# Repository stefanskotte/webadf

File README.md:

# WebFloppy

An Amiga disk library that puts a disk in a real Amiga's floppy drive over WiFi. (The repository keeps the
project's first name, `webadf`.)

Two halves that work together:

- **A web app** for keeping Amiga disk images. Add them, have them identified
  against TOSEC, OpenRetro and Demozoo, organise them into collections, browse and
  edit the files inside a disk, rewind a disk to any earlier version, and send files to
  and from the Amiga.
- **A drive replacement.** An RP2350 board plugs into the Amiga's floppy connector,
  behaves like a DD or HD floppy drive, and plays whichever disk you pick in the web app.
  When the Amiga saves, the changes go back to the library.

Run the web app two ways: use our hosted copy at <https://webadf.vercel.app> (on Vercel), or
host your own with Docker on any amd64 or arm64 machine, a NAS included. A self-hosted copy has every
feature the hosted one has. Firmware updates, the PaulaNET driver disk and the TOSEC catalogue
arrive by themselves; see [docs/self-hosting.md](docs/self-hosting.md).

Pick a disk in the browser, or tap its NFC tag on the drive, and the Amiga reads it.
Workbench 3.1 boots from the board, games load, and saves made on the Amiga show up
in the web app as new versions of the disk.

*Rev B, designed by Shanshe: 34-pin floppy header, floppy power connector, OLED
display, buzzer, a 4-pin header (J4), and a Pimoroni Pico Plus 2 W.
The KiCad project is in `wifi-floppy/hardware/`; check it with `pnpm hw:verify` before
ordering. Rev B has been the bench board since October 2026.*

## Bugs and ideas

Found a bug, or want something WebFloppy does not do yet? Anyone can open an issue at
<https://github.com/stefanskotte/webadf/issues>, for a bug report or a feature request alike. For a bug, say what
you did, what you saw and, for a board, which firmware it runs (Devices shows it).

## Quickstart

Choose where the web app runs. The board's first install is the same either way; only a
self-hosted copy needs one extra step, pointing the board at your server.

### Path A: the hosted web app (Vercel)

You need the board, a USB cable, a phone and an account on <https://webadf.vercel.app>
(registration is by invitation). The board talks to this server out of the box.

1. Hold the **BOOT** button (the Raspberry Pi docs call it BOOTSEL) and plug the board into
   your computer over USB. A drive called `RP2350` appears.
2. Download `wifi-floppy-install-<version>.uf2` from the
   [latest release](https://github.com/stefanskotte/webadf/releases/latest) and drag it onto
   that drive. The board writes it and restarts by itself; the drive disappears.
3. **Get a pairing code in the web app.** The code comes from the web app, not the board. Open
   **Devices**: with no board yet it lists the five steps (**How pairing works** shows them again at any
   time). Press **Pair a device**, give the board a name and press **Get a code**. The code lasts 30 minutes,
   and the page now walks you through the rest with the code filled in.

4. **Give the board your Wi-Fi and the code.** Power the board; its screen shows *Setup needed* and its own
   Wi-Fi network, `wifi-floppy-XXXX`. Join that network from your phone (password `wififloppy`). The
   setup page opens by itself; if it does not, browse to `http://192.168.4.1/`. Enter your home Wi-Fi name
   and password (a 2.4 GHz network with a password) and the code, and press **Save**.

5. **Wait about a minute.** The board's network disappears, the board joins your Wi-Fi and uses the code
   to register with the web app. Keep the Devices page open: it says **Paired** and shows the board by
   itself. If the board cannot join or register, its setup network comes back with the reason at the top
   of the setup page; join it again and fix that. Firmware updates now arrive over the air from the web app.

### Path B: your own server (self-hosted, Docker)

You need a host with Docker and Compose v2, the board, a USB cable and a phone.

1. Install the stack, as [docs/self-hosting.md](docs/self-hosting.md#2-install) describes: download
   `compose.yaml` and `.env.example` (as `.env`) from the newest `web-X.Y.Z` tag, set `WEBADF_URL`
   (for example `https://192.168.1.10`) and `WEBADF_ADMIN_EMAIL` in `.env`, then run
   `docker compose up -d`. Create the account with the link from `docker compose logs app | grep 'first admin'`.
2. Install the firmware as in steps 1-2 of Path A.
3. **Override the server.** The firmware points at the hosted app by default. Open the board's
   USB serial console (any serial terminal, firmware 1.13.0 or newer) and type:

   ```
   wf server set https://192.168.1.10
   wf server tls noverify
   YES
   wf reboot
   ```

   Use your own `WEBADF_URL`. `tls noverify` is needed because a board cannot trust the
   certificate Caddy makes for an IP address or a LAN name; with a public `WEBADF_DOMAIN` and a
   Let's Encrypt certificate, leave it out. `wf server show` prints the setting and
   `wf server clear` goes back to the hosted app. Changing the server forgets the board's
   Wi-Fi and pairing, and it refuses while a disk is mounted.
4. Pair it as in steps 3-5 of Path A, from **Devices** on your own server. Firmware updates come
   from your server too: it imports every signed release from GitHub daily.

If your phone has joined this board's setup network before, forget that network first. More
detail, and what to do when a join fails, is in
[wifi-floppy/README.md](wifi-floppy/README.md#first-install) and, for a self-hosted copy,
[docs/self-hosting.md](docs/self-hosting.md#4-boards).

## Screenshots

The pictures come from a demo account holding freely redistributable disks: scene demos and
freeware tools. `PORT=3100 pnpm screenshots` takes them again (see
`e2e/screenshots.shots.ts`); every email address on them is masked, and the board is a
stand-in called A500. The one exception is Transfer's window, captured from a real A500 by hand.

*The library. Titles are identified against TOSEC and Demozoo; the 9 Fingers card is
outlined and carries a DF0 pill because its disk is in a drive.*

*The drive menu in the header: from any page, see what each board is playing, switch write
protection, step to the next disk or eject.*

*A title page: facts and screenshots from Demozoo, then each disk with its actions.*

*Files: two panes in the Directory Opus style over STASH:, NET: and LIBRARY: (collections are folders there). The pane
you last clicked is the source; the buttons under the panes act on it. Each edit to a disk is a new version in its History.*

*NET: also lists the Amiga's own volumes when Transfer runs there with Read ticked: open a drawer on the hard disk
and copy files to STASH: or LIBRARY:. With Write ticked too, copy and move onto it, rename and delete.*

*Transfer, on the Amiga itself: files from the web app arrive here, and Send goes the other way. Read and Write decide
what the web app may do with the Amiga's volumes.*

*A board on the Devices page. The drawing's screen shows what the board's OLED shows.*

*The display editor: choose the panel, then which elements the OLED draws and where.*

*Adding disks: drop them anywhere on the Library page, or use Add disks (Browse files, Paste a URL). The tray says
what each one did.*

*Help explains the parts that are not obvious.*

*Settings has three tabs: Account (yours alone), Library (sharing) and Server.*

*Sharing, on the Library tab: let a friend's WebFloppy browse and mount your collections. Each link works once.*

*About this server, on the Server tab.*

*On a phone or a tablet (below 1024 px wide), the pages move to a tab bar at the bottom; More holds the rest.*

*The server admin's Overview, for whoever runs the copy.*

## Features

### Library

- Add `.adf`, `.adz`, `.dms`, `.dmz` and `.hfe` by dropping them anywhere on the Library page (folders and
  `.zip` / `.lha` of them too) or through Add disks: Browse files, or Paste a URL to one (or to a `.zip` or `.lha`
  of them, up to 20 MB). Drop `.lha`, `.lzh` and `.zip` archives onto a disk to pick files out of them.
- HD (1.76 MB) ADFs are recognised and tagged HD, and are disks like any other: browsed
  and edited in the browser, with full history.
- Each unique disk is stored once, however many times it is added.
- Disks are identified against TOSEC, OpenRetro and Demozoo, and grouped into titles
  with cover art, screenshots, publisher, year and type.
- A grid of cards or a condensed table, a page at a time; collections (folders in the table),
  disk sets for multi-disk games, and search from the header.
- Create a blank formatted disk: 880 KB or 1.76 MB, OFS or FFS.
- Download any disk as an ADF.
- Works on a phone: below 1024 px the pages move to a tab bar at the bottom.

### Files

- The Files page: two panes over three places. LIBRARY: holds your titles and their disks; STASH: keeps loose
  files for 30 days (what you drop there, and what your Amiga sends); NET: holds what waits to go to each board's
  Amiga, and the Amiga's own volumes. Copy and move between the panes, or drag.
- Browse the AmigaDOS filesystem in the browser: files, folders, free space.
- Add, rename, move and delete files and folders; drop a folder from your computer
  onto a disk; drag entries between folders.
- Every change is a new version. The history panel shows what changed in each
  version, lets you browse any old version, and restores one as a new version.
- HFE images (including long-track formats such as Turrican's) play read-only and can
  be extracted to an ADF when every sector decodes.

### The drive

- Set up from a phone: the board opens a WiFi setup page, you enter your network and
  a pairing code from the web app, and it joins your library.
- Mount and eject from the web app, from the drive menu in the header, or by
  tapping an NFC tag. Next disk steps a multi-disk game on, and the board loads that disk
  ahead of time.
- Reads and writes on a real Amiga. Saves reach the library as new disk versions,
  including saves made while the board was offline.
- Works as DF0, beside a real DF1. Or the board is DF1 as well: holding the next disk of the
  set, or any disk you mount there.
- Plays HD disks: the board tells the Amiga it is an HD drive while an HD disk is in.
  Needs Kickstart 3.0 or later. Playing needs firmware 1.4.1 or later (the web app
  refuses to mount an HD disk on older firmware and says so); saving to an HD disk
  needs 1.5.0 (1.4.x keeps HD write-protected on the board whatever the web app
  says).
- Write protection can be switched from the web app while the disk is in the drive.
- OLED status display (128x32 or 128x64, SSD1306 or SH1106): WiFi strength, what it is
  doing, the disk's name and the current track. A display editor in the web app picks what
  it shows and where. An activity LED blinks on reads.
- Updates its own firmware from the web app. Releases are signed, a failed update
  falls back to the previous firmware, and the board never updates while a disk is
  in the drive.

### Amiga networking

- The board can put the Amiga on your network as DF1, with Rob Smith's PaulaNET driver
  (used with his permission) and a TCP/IP stack such as AmiTCP_NG or Roadshow. The driver disk
  comes from the board itself.
- Send files from your computer, or from a disk in your library, to a folder on the Amiga: on the Files page,
  drop them on Send files to the Amiga, or copy them into a board under NET:. Files the Amiga sends back land in STASH:.
- Transfer, the Amiga program on the driver disk, saves what arrives and sends files up. It runs from Workbench,
  from a Shell, or hidden from WBStartup as a commodity (Ctrl-Alt-W shows it).
- With Transfer's Read ticked, the Files page browses the Amiga's own volumes; with Write ticked too, it copies and
  moves onto them, makes drawers, renames and deletes. Both are off until the Amiga's owner ticks them.
- Setting it up, Transfer, the limits and what to do when something fails:
  [docs/amiga-networking.md](docs/amiga-networking.md).

### NFC tags

- Tap a tag on the drive to mount its disk. Tapping another tag swaps disks; tapping
  the one already in the drive does nothing. A Next-disk card steps to the next disk.
- Write any disk to a tag from the ⋯ menu on its library card, or the NFC button on a
  disk, then tap a tag on the drive; the result appears in the browser.
- A tag only ever mounts disks from your own library.
- Reader: HW-147C (Si512), on the board's I2C bus next to the OLED. PN532 modules work
  from firmware 1.18.0 and are still being tested.

## How it works

An Amiga floppy drive does not deliver blocks. It hands Paula a raw magnetic flux
stream and the Amiga decodes MFM in software, so a drive emulator has to produce flux
at the right rate, continuously, while the disk spins.

```
  browser  ──mount──▶  web app  ──encodes ADF → MFM──▶  device  ──flux──▶  Amiga
     ▲                    │                                │
     └──── new version ◀──┴── Postgres + blobs     RP2350 + 8 MB PSRAM ◀── NFC tag
```

The server encodes a 901,120-byte ADF into 2,027,536 bytes of Amiga MFM and the board
streams it: PIO emits 2 µs bitcells, DMA restarts each revolution and raises INDEX,
giving 300 rpm. The whole disk lives in PSRAM, so a seek is answered immediately
instead of over the network. The board streams flux rather than ADFs, which lets
flux formats such as HFE use the same path.

An HD disk is the exception. The server sends the board the ADF itself (a small
WFAD header, then 1,802,240 bytes), and the board encodes each track to MFM as the
head reaches it, in about 4 ms, well inside the head's settle time. A PIO program
answers the Amiga's drive-ID read on RDY with the HD ID while an HD disk is mounted.
When the Amiga saves to an HD disk, the board checks all 22 sectors of the written
track, keeps them as ADF bytes, and uploads those bytes as they are.

When the Amiga writes, the board decodes the written tracks, uploads them, and the
server records them as a new version of the disk. Versions are stored as sector
deltas.

## Status

| | |
|---|---|
| Web app: library, collections, identification, search | live |
| Add `.adf` `.adz` `.dms` `.hfe` to the library; `.lha`/`.lzh`/`.zip` onto a disk | live |
| File editing inside a disk, blank disks, drag and drop | live |
| Disk history: browse and restore any version | live, restore verified on hardware |
| Device: setup portal, WiFi, TLS, pairing | verified on hardware |
| Mount and eject from the browser and the header's drive menu | verified on hardware |
| Reading on a real Amiga (Workbench 3.1, games) | verified on hardware |
| Writing on a real Amiga, saves reach the library | verified on hardware |
| Second drive (DF1) alongside the board | verified on hardware |
| HFE, including long-track (Turrican) | verified on hardware; weak-bit titles not yet tested |
| HD disks, read-only (Kickstart 3.0+) | verified on hardware (firmware 1.4.1, Kickstart 3.1) |
| HD disks: Amiga saves, history, browser editing, blank HD disks | shipped in firmware 1.5.1; bench steps 4-7 owed (HANDOFF 3ao) |
| Firmware updates from the web app | verified on hardware (current release: 1.21.1) |
| Self-hosting with Docker (compose stack, GHCR image, amd64 + arm64) | live (web-1.1.0); verified with a board and an A500 on an openmediavault NAS |
| NFC: tap to mount, write tags from the web | verified on hardware |
| Amiga networking (PaulaNET as DF1), files to and from the Amiga | verified on hardware (A500) |
| Rev B board | built and running (Shanshe's design, `wifi-floppy/hardware/`) |

## Repository

| Path | What |
|---|---|
| `src/` | the Next.js app |
| `src/lib/adfmfm/` | ADF ⇄ Amiga MFM encoder, verified against Greaseweazle |
| `src/lib/adffs/` | AmigaDOS filesystem reader/writer (OFS/FFS) |
| `src/lib/archive/` | `.lha`/`.lzh`, `.zip` and `.dms` decoders, all browser-side |
| `src/lib/hfe/` | HFE parsing, conversion for the board, ADF extraction |
| `src/lib/disk-history/` | sector deltas and the version chain behind history and restore |
| `src/lib/nfc/` | NFC tap and tag-writing rules and storage |
| `wifi-floppy/firmware/` | the RP2350 firmware (pico-sdk ≥ 2.3.0) |
| `wifi-floppy/hardware/` | the board (KiCad) |
| `docs/superpowers/specs/` | design specs, one per feature |
| `HANDOFF.md` | the engineering log: decisions, measurements, bench results |

## Running it

```bash
pnpm install
pnpm db:dev start         # a local Postgres 18 in Docker; prints its DATABASE_URL
pnpm db:migrate           # apply drizzle/ to DATABASE_URL (there is no db:push)
pnpm dev                  # needs .env.local: DATABASE_URL, BETTER_AUTH_SECRET,
                          # BETTER_AUTH_URL (BLOB_READ_WRITE_TOKEN is optional)
pnpm test                 # vitest, pure logic
pnpm e2e                  # playwright, against the database in .env.local
bash scripts/e2e-local.sh # playwright with no Vercel or Neon: a fresh Postgres in
                          # its own container (webadf-pg-e2e, :55433 -- never the
                          # db:dev one) and local storage; arguments go to playwright
```

Stored files (disk images, covers, firmware) go to local disk under `./data/blobs`
(`STORAGE_DIR` moves it) unless `BLOB_READ_WRITE_TOKEN` is set, in which case they go to
Vercel Blob. On Vercel the token is required: the app refuses to fall back to local disk there.

To run your own copy, use the Docker stack in [docs/self-hosting.md](docs/self-hosting.md)
(Quickstart, [Path B](#path-b-your-own-server-self-hosted-docker)); the commands above are for development.

A self-hosted copy needs no extra setting: Settings → About this server (`/about` leads there) reads
**Self-hosted** unless `SELFHOSTED=false`, which only our own deployment sets. A Docker build
without `.git` can pass `GIT_SHA` so About this server shows the commit.

Firmware:

```bash
export PICO_SDK_PATH=/path/to/pico-sdk        # tag 2.3.0 or later
pnpm firmware:build
pnpm firmware:test                            # host tests, no board needed
pnpm firmware:publish --dry-run               # sign and register a release
```

Write a disk to an NFC tag from the command line:

```bash
pnpm nfc:write "Turrican II disk 1"           # then tap a tag on the drive
```

The setup access point uses the password **`wififloppy`** by default. Set
`PORTAL_AP_PASSWORD` at build time to change it. The pairing code from the web app is
what authorises a board to join a library.

Putting the firmware on a new board is the [Quickstart](#quickstart) above: one
`wifi-floppy-install-<version>.uf2` from the GitHub release, dragged onto the drive that
appears while BOOT is held at power-up. With picotool, `pnpm firmware:install-partitioned` still works.

Every push that touches the firmware is built by
[`.github/workflows/firmware.yml`](.github/workflows/firmware.yml), which runs the host
tests and publishes a `.uf2` with a `manifest.json` (version, commit, size, SHA-256).

## Verification

Each layer that talks to hardware or to an undocumented format is checked against an
independent implementation:

| | checked against |
|---|---|
| `pnpm adfmfm:diff` | Greaseweazle's `amigados` codec |
| `pnpm adffs:verify` | `xdftool` |
| `pnpm lha:verify` | the real `lha` binary |
| `pnpm dms:verify` | xDMS, the implementation ours was ported from |

## Licence

- **Software** (the web app, scripts and the wifi-floppy firmware source): [MIT](LICENSE).
- **Hardware** (`wifi-floppy/hardware/`, the board design): [CERN-OHL-P-2.0](wifi-floppy/hardware/LICENSE), the
  permissive open-hardware licence, so anyone can build, modify and sell their own boards. The rev B PCB layout is
  Shanshe's work, licensed this way with Shanshe's agreement; see
  [wifi-floppy/hardware/NOTICE.md](wifi-floppy/hardware/NOTICE.md).
- **Third-party code, the libraries in the firmware image, and acknowledgements**: see
  [THIRD-PARTY-NOTICES.md](THIRD-PARTY-NOTICES.md). The Wi-Fi driver bundled with the Pico SDK is licensed for use
  on Raspberry Pi chips (which this board is).

This project builds on Nano-Tek, OpenFlops, Keir Fraser's FlashFloppy and Greaseweazle, and the other work credited
in the notices file.

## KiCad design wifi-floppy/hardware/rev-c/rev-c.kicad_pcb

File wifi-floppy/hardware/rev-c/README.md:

# Rev C: on-board RP2350, schematic and routed board

Rev B with the PIM726 module replaced by its parts on our PCB: RP2350B, 16 MB flash, 16 MB PSRAM, RM2 radio, crystal, core regulator, USB-C, BOOTSEL, SWD. Every GPIO stays where the PIM726 has it, so the firmware's pin map and the pico-sdk board definition are unchanged. Same outline as rev B. Rev B's files are untouched.

**The schematic and the routed board agree, and nothing else about the board differs from using a PIM726 on rev B. It is still not a board to order:** see "Owed before a fab order".

## Result (2026-11-05)

| Check | Result |
|---|---|
| Layers | 4: signals on F.Cu and B.Cu, GND on In1, +3.3 V on In2 |
| KiCad DRC, with schematic parity | 0 unconnected, 0 errors, 0 parity differences. 24 silkscreen warnings, 21 of them M1's outline over its own pads, and one 0.03 mm neck somewhere in the top ground pour, not located |
| ERC | 0 errors, 0 warnings |
| `verify_sch.py` | all 75 multi-pin nets match, whatever they are called |
| `verify_pins.py rev-c.kicad_pcb` | 209 of 209 against the RP2350 datasheet, firmware `board.c`, the pico-sdk header, the RM2 datasheet, and rev B's connected pads |
| `verify_reg.py` | the regulator matches Raspberry Pi's pattern: 62 differences before, 0 now |
| `pnpm hw:verify rev-c` | passes: ERC, DRC, firmware pins, J1 lines, 1k pull-ups, the regulator |
| Gerbers | analysed with kicad-happy. Not yet through JLC's own check |
| Tracks | 0.15 mm, necked as low as 0.09 mm at the QFN, vias 0.45/0.2 mm, spacing 0.127 mm: within JLC's published 4-layer limits, not confirmed by JLC |

## Parts

From Pimoroni's Pico Plus 2 W schematic unless noted.

| Ref | Part | Note |
|---|---|---|
| U1 | RP2350B, QFN-80 | |
| U3 | W25Q128JVSIQ, SOIC-8 208 mil | Pimoroni's schematic names W25Q128JVPIQ: same family and capacity, check the package suffix when buying |
| U4 | IS66WVS16M8FBLL-104NLI, SOIC-8 150 mil | **16 MB, not Pimoroni's 8 MB.** APS6404L-3SQR is pin-compatible and fits the same pads |
| M1 | Raspberry Pi RM2 | Own antenna. Hand-made footprint from RM2 datasheet figure 6 |
| U5 | NCP1117ST33T3G, SOT-223 | **Not Pimoroni's AP7366** (the 2026-10-20 rev C note's part, easier to solder and cool) |
| L1 | Abracon AOTA-B201610S3R3-101-T | Raspberry Pi's polarity-marked inductor, LCSC C42411119. **Not Pimoroni's MLZ2012M3R3HT000**: see "Core regulator" |
| Y1 | Abracon ABM8-272-T3, 15 pF load caps | Raspberry Pi's crystal, LCSC C20625731; JLC's RP2350B page names the same one |

Left out as nothing here uses them: the VSYS sense divider and its MOSFET, the 1k links from GP26-28 to GP40-42, the user switch, the Qw/ST connector (its GP4/GP5 are MTR and DIR here; operator confirmed 2026-11-05), the 40-pin header.

The reset button is out (operator, 2026-11-05: BOOTSEL is needed, PIM726's RESET is not). Test pad TP1 on RUN replaces it; RUN keeps its internal pull-up (RP2350 pin table), as on Pimoroni's sheet.

**Scope (operator, 2026-11-05): everything stays as it is with a PIM726.** So the J5 DRIVE passthrough, Amiga RESET line and keyed I2C connectors from the earlier rev C plan are not on this board. Firmware does not use what is left out: GP26-28, GP43 and GP45 appear in comments only.

## Schematic

`rev-c.kicad_sch` is rev B's sheet with the module out. `mcu.kicad_sch` (RP2350B, supplies, crystal, RM2) and `support.kicad_sch` (USB-C, 3.3 V, flash, PSRAM, BOOTSEL, debug) hold the module's parts, after Pimoroni's sheets. `rev-c-schematic.pdf` is the print. All new symbols are in `rev-c-lib.kicad_sym`; apart from RM2 (drawn from RM2 table 2) and the PSRAM (KiCad's APS6404L with ISSI's value) they are KiCad's own.

The sheets are the source: edit them in KiCad. `build_board.py` reads their netlist for names, values, footprints and links, which is why parity is clean. Swapping MTR and DIR, or removing a PWR_FLAG and a no-connect, in a copy made `verify_sch.py` fail, as it should.

Differences from Pimoroni: the core regulator and crystal (below), NCP1117 with 10 uF either side (AP7366, 2.2 uF; the 2026-10-20 note's part), 16 MB PSRAM, 10 uF added at RM2's VDDBAT, BOOTSEL as 1k and switch without their diode and user-switch network. Pull-ups (flash CS 3k3, PSRAM CS 100k) and the USB series resistors (27.4 ohm) are Pimoroni's.

## Core regulator

Operator's decision, 2026-11-05: Raspberry Pi's pattern, an exception to "same as a PIM726". `reg_pattern.py` holds it, taken from Raspberry Pi's RP2350 minimal design R4 (MIT, see `../NOTICE.md`) and datasheet section 6.3.8; `verify_reg.py` checks the board and sheets against it. The VREG pins have the same order and pitch on our QFN-80 as on the QFN-60 it was drawn for.

| | Pimoroni's sheet, and rev C before | Now | Datasheet |
|---|---|---|---|
| L1 | MLZ2012M3R3HT000, about 350 mA, 260 mOhm max, unmarked | AOTA-B201610S3R3-101-T, 2.4 A, 140 mOhm max, marked | at least 1.5 A, at most 250 mOhm, polarity-marked |
| COUT, C23 | 10 uF | 4.7 uF | 4.7 uF +/-20% |
| CIN, C21 | 10 uF | 4.7 uF | at least 4.7 uF |
| RFILT, CFILT (R20, C22) | 27.4 ohm, 2.2 uF | 33 ohm, 4.7 uF | Raspberry Pi's design |
| Second COUT, C15 at DVDD pin 32 | 100 nF | 4.7 uF | recommended |

LX is 4.0 mm on the top layer with no vias. In1 is cut away under L1 and LX (figure 24). The top pour stays out, so the regulator's high-current ground meets the rest at two vias, and CFILT has its own via. VREG_FB comes from COUT, and COUT reaches the DVDD ring by a 0.6 mm track on the back, as Raspberry Pi route it. Moving one of these parts means moving them all.

**L1 has a right way round.** Pad 1, the dot, goes to DVDD: the symbol was flipped so its pin 1 is DVDD. RPROM's README warns that JLC's placement file needed L1's orientation fixing by hand: check it on the assembly preview.

The pattern is copied, not proven here: Raspberry Pi test it on their board, and no rev C board has been built. CIN and COUT need low ESR (50 and 250 mOhm); Raspberry Pi use GRM155R60J475ME47D for all three 4.7 uF parts.

## RM2 antenna

The module sits in the bottom right corner with its antenna on the board edge. Of Raspberry Pi's 35.5 x 18.5 mm keep-out, only 26 x 5 mm is on the board; the rest is air. It is a rule area on all layers, about where rev B's was. In a case, what is beyond the edge also counts.

## 16 MB PSRAM: what is and is not known

The operator confirms the RP2350B supports 16 MB of PSRAM (2026-11-05). What follows is what was checked here.

From the ISSI datasheet and `hardware_psram/psram.c`: same pinout and commands as the APS6404 (35h, EBh with 6 wait cycles, 38h), 2.7-3.6 V, 1024-byte pages. The pico-sdk's size detection names ISSI's 16 MiB ID, and it breaks bursts at 1024 bytes, so a burst cannot cross the part's two stacked dies (its datasheet forbids that). **None of it has run on hardware.** Firmware needs `PICO_PSRAM_SIZE_BYTES` and `SLOT_COUNT` raised to use more than 8 MB.

## Owed before a fab order

1. **A person reading the schematic.** Nobody has yet.
2. **A person checking the core regulator against datasheet figures 23 and 24**, and the crystal: Y1's placement and tracks are still autorouted, its part and caps are now Raspberry Pi's.
3. **A person reading the autorouted copper:** QSPI lengths, the USB pair (12 Mbit/s, so no impedance control needed, but keep it short), the floppy lines. It has too many vias.
4. **Footprints against samples:** RM2, USB-C, buttons.
5. **Board-edge clearances:** SW1 moved in 0.3 mm, now about 0.55 mm. M1 at the edge is intended.
6. **Sourcing:** not checked. The JLC search was down; JLCONE not used.
7. **Heat:** 5 V to 3.3 V at Wi-Fi peaks is about 0.7 W in U5. Measure it.

## Rebuild

In order, with KiCad's Python and Freerouting 2.5.0: `variants.sh` runs `build_board.py` (places), `regulator.py` (the regulator's copper), `stitch.py` (joins power pins to the planes), Freerouting on the outer layers, and `route.py` (adds the planes and pours), into `v1/`. Then by hand: `clean.py v1/rev-c.kicad_pcb v1/drc1.json` removes the router's stray vias and widens any neck below 0.09 mm, `finish.py` adds fiducials and sets the silkscreen, `verify_pins.py` checks. The fiducials landed at free spots, not in the corners: place them properly in KiCad. Part references on the new parts are hidden until someone places them.

`package.sh` builds `rev-c-kicad-project.zip`: the project with `wifi-floppy-lib` copied in and the library tables pointed at the copies, so it opens anywhere with KiCad 10. Rebuild it after any change.

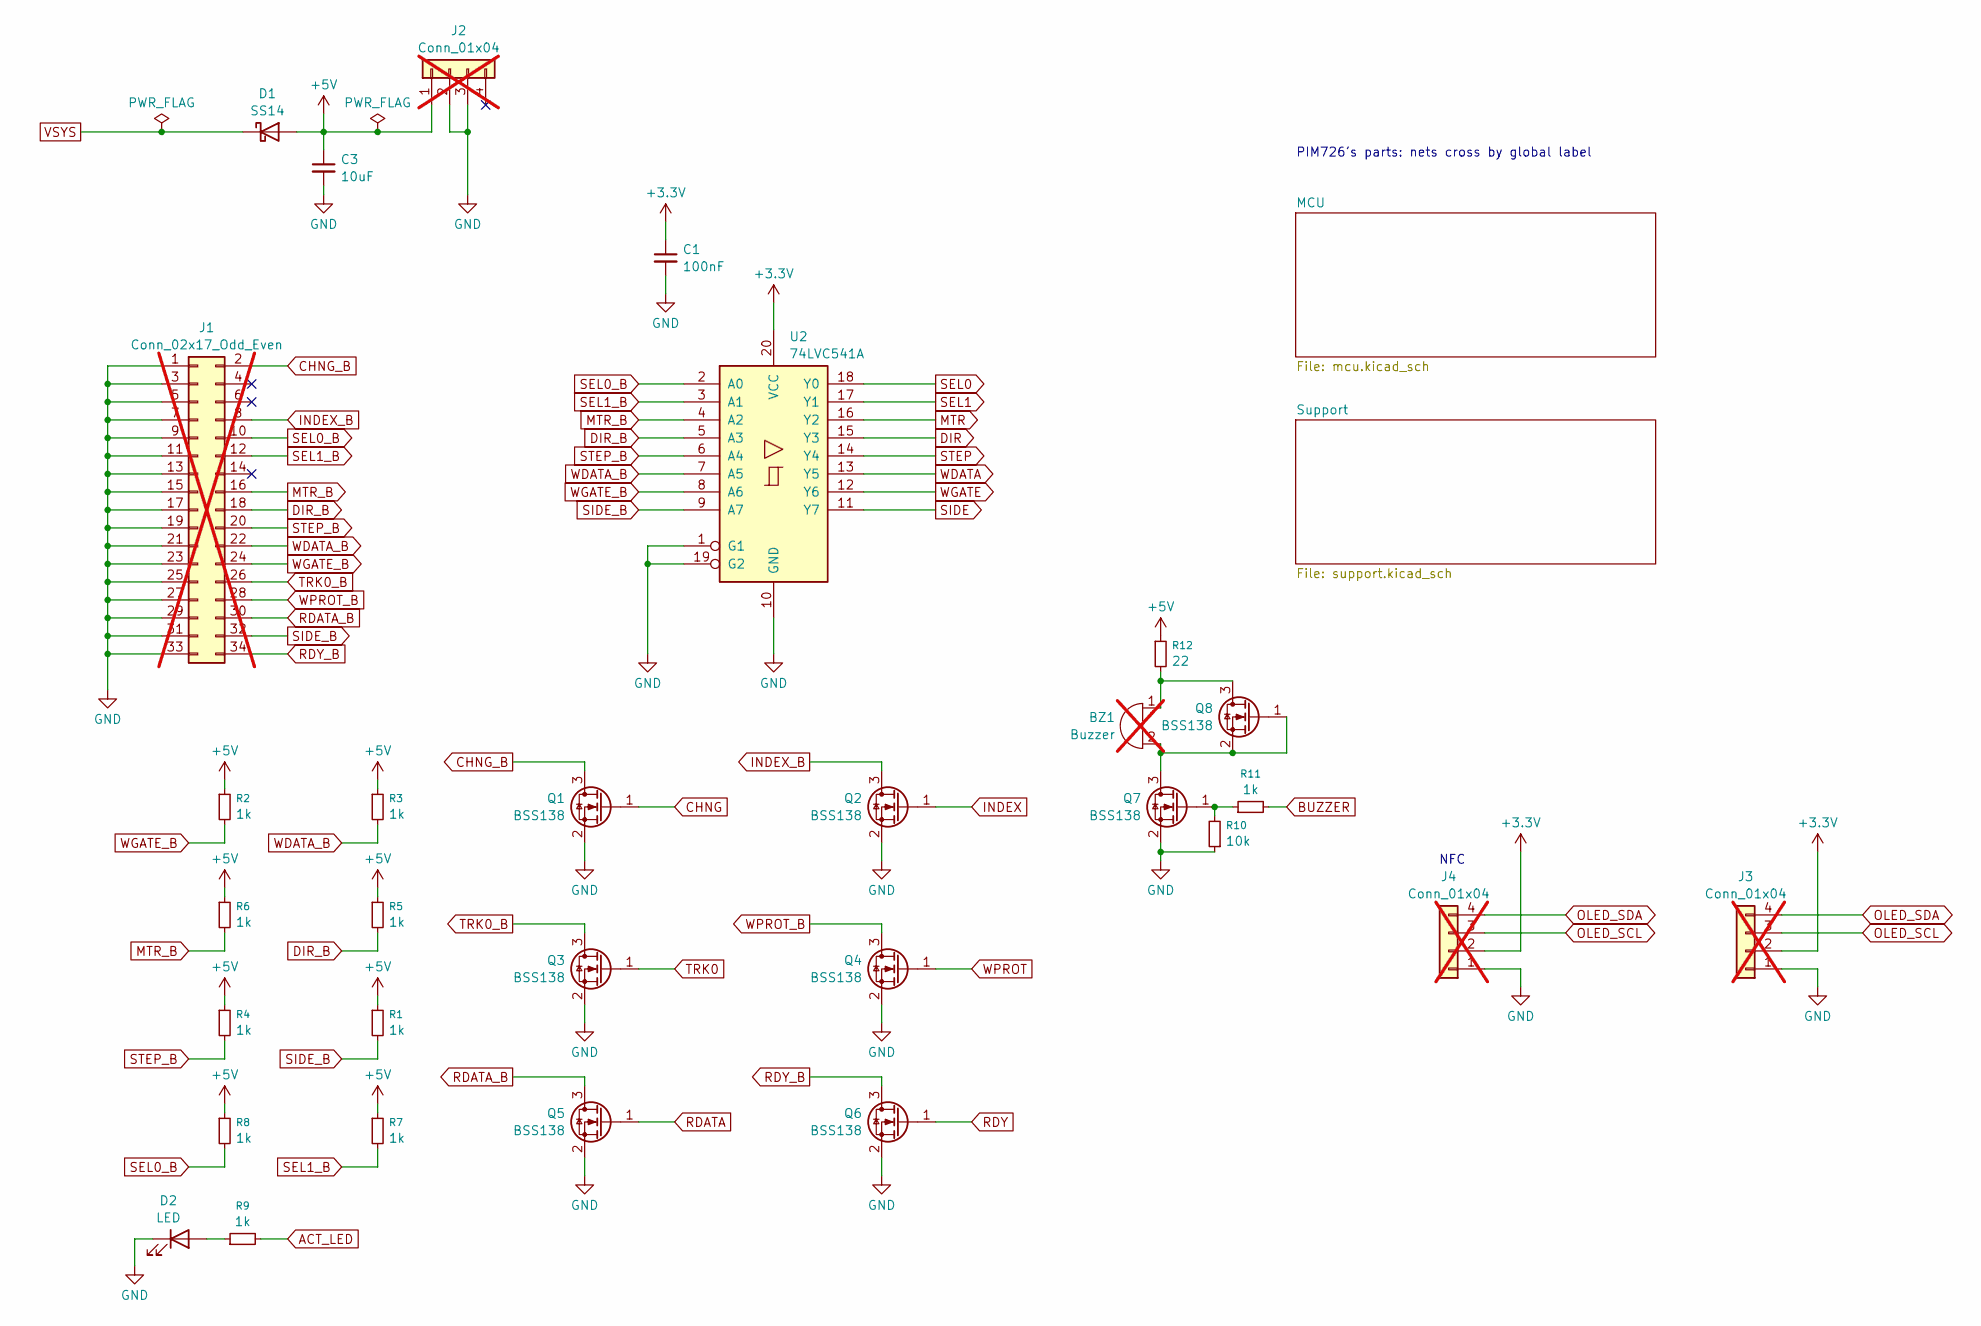
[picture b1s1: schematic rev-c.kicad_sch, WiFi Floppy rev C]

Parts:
BZ1: Buzzer; Buzzer_TDK_PS1240P02BT_D12.2mm_H6.5mm; LCSC C2687681; not fitted
C1: 100nF; C_1206_3216Metric_Pad1.33x1.80mm_HandSolder
C3: 10uF; C_1206_3216Metric_Pad1.33x1.80mm_HandSolder
D1: SS14; D_SMA_Handsoldering
D2: LED; LED_1206_3216Metric_Pad1.42x1.75mm_HandSolder; LCSC C49018
J1: Conn_02x17_Odd_Even; IDC-Header_2x17_P2.54mm_Vertical; LCSC DNP; not fitted
J2: Conn_01x04; PinHeader_1x04_P2.54mm_Horizontal; LCSC DNP; not fitted
J3, J4: Conn_01x04; PinHeader_1x04_P2.54mm_Vertical; LCSC DNP; not fitted
Q1, Q2, Q3, Q4, Q5, Q6, Q7, Q8: BSS138; SOT-23
R1, R2, R3, R4, R5, R6, R7, R8, R9, R11: 1k; R_1206_3216Metric_Pad1.30x1.75mm_HandSolder; LCSC C1469
R10: 10k; R_1206_3216Metric_Pad1.30x1.75mm_HandSolder; LCSC C1489
R12: 22; R_1206_3216Metric_Pad1.30x1.75mm_HandSolder; LCSC C2925020
U2: 74LVC541A; SOIC-20W_7.5x15.4mm_P1.27mm; LCSC DNP

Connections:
+3.3V: C1.1, J3.2, J4.2, U2.20 (VCC); also elsewhere on the board
+5V: C3.1, D1.2 (A), J2.1, R1.1, R2.1, R3.1, R4.1, R5.1, R6.1, R7.1, R8.1, R12.1
ACT_LED: R9.2; also elsewhere on the board
BUZZER: R11.2; also elsewhere on the board
CHNG: Q1.1 (G); also elsewhere on the board
CHNG_B: J1.2, Q1.3 (D)
DIR: U2.15 (Y3); also elsewhere on the board
DIR_B: J1.18, R5.2, U2.5 (A3)
GND: C1.2, C3.2, D2.1 (K), J1.1, J1.3, J1.5, J1.7, J1.9, J1.11, J1.13, J1.15, J1.17, J1.19, J1.21, J1.23, J1.25, J1.27, J1.29, J1.31, J1.33, J2.2, J2.3, J3.1, J4.1, Q1.2 (S), Q2.2 (S), Q3.2 (S), Q4.2 (S), Q5.2 (S), Q6.2 (S), Q7.2 (S), R10.1, U2.1 (G1), U2.10 (GND), U2.19 (G2); also elsewhere on the board
INDEX: Q2.1 (G); also elsewhere on the board
INDEX_B: J1.8, Q2.3 (D)
MTR: U2.16 (Y2); also elsewhere on the board
MTR_B: J1.16, R6.2, U2.4 (A2)
unnamed: BZ1.1 (+), Q8.3 (D), R12.2
unnamed: BZ1.2 (-), Q7.3 (D), Q8.1 (G), Q8.2 (S)
unnamed: D2.2 (A), R9.1
unnamed: Q7.1 (G), R10.2, R11.1
OLED_SCL: J3.3, J4.3; also elsewhere on the board
OLED_SDA: J3.4, J4.4; also elsewhere on the board
RDATA: Q5.1 (G); also elsewhere on the board
RDATA_B: J1.30, Q5.3 (D)
RDY: Q6.1 (G); also elsewhere on the board
RDY_B: J1.34, Q6.3 (D)
SEL0: U2.18 (Y0); also elsewhere on the board
SEL0_B: J1.10, R8.2, U2.2 (A0)
SEL1: U2.17 (Y1); also elsewhere on the board
SEL1_B: J1.12, R7.2, U2.3 (A1)
SIDE: U2.11 (Y7); also elsewhere on the board
SIDE_B: J1.32, R1.2, U2.9 (A7)
STEP: U2.14 (Y4); also elsewhere on the board
STEP_B: J1.20, R4.2, U2.6 (A4)
TRK0: Q3.1 (G); also elsewhere on the board
TRK0_B: J1.26, Q3.3 (D)
VSYS: D1.1 (K); also elsewhere on the board
WDATA: U2.13 (Y5); also elsewhere on the board
WDATA_B: J1.22, R3.2, U2.7 (A5)
WGATE: U2.12 (Y6); also elsewhere on the board
WGATE_B: J1.24, R2.2, U2.8 (A6)
WPROT: Q4.1 (G); also elsewhere on the board
WPROT_B: J1.28, Q4.3 (D)

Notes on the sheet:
PIM726's parts: nets cross by global label
NFC

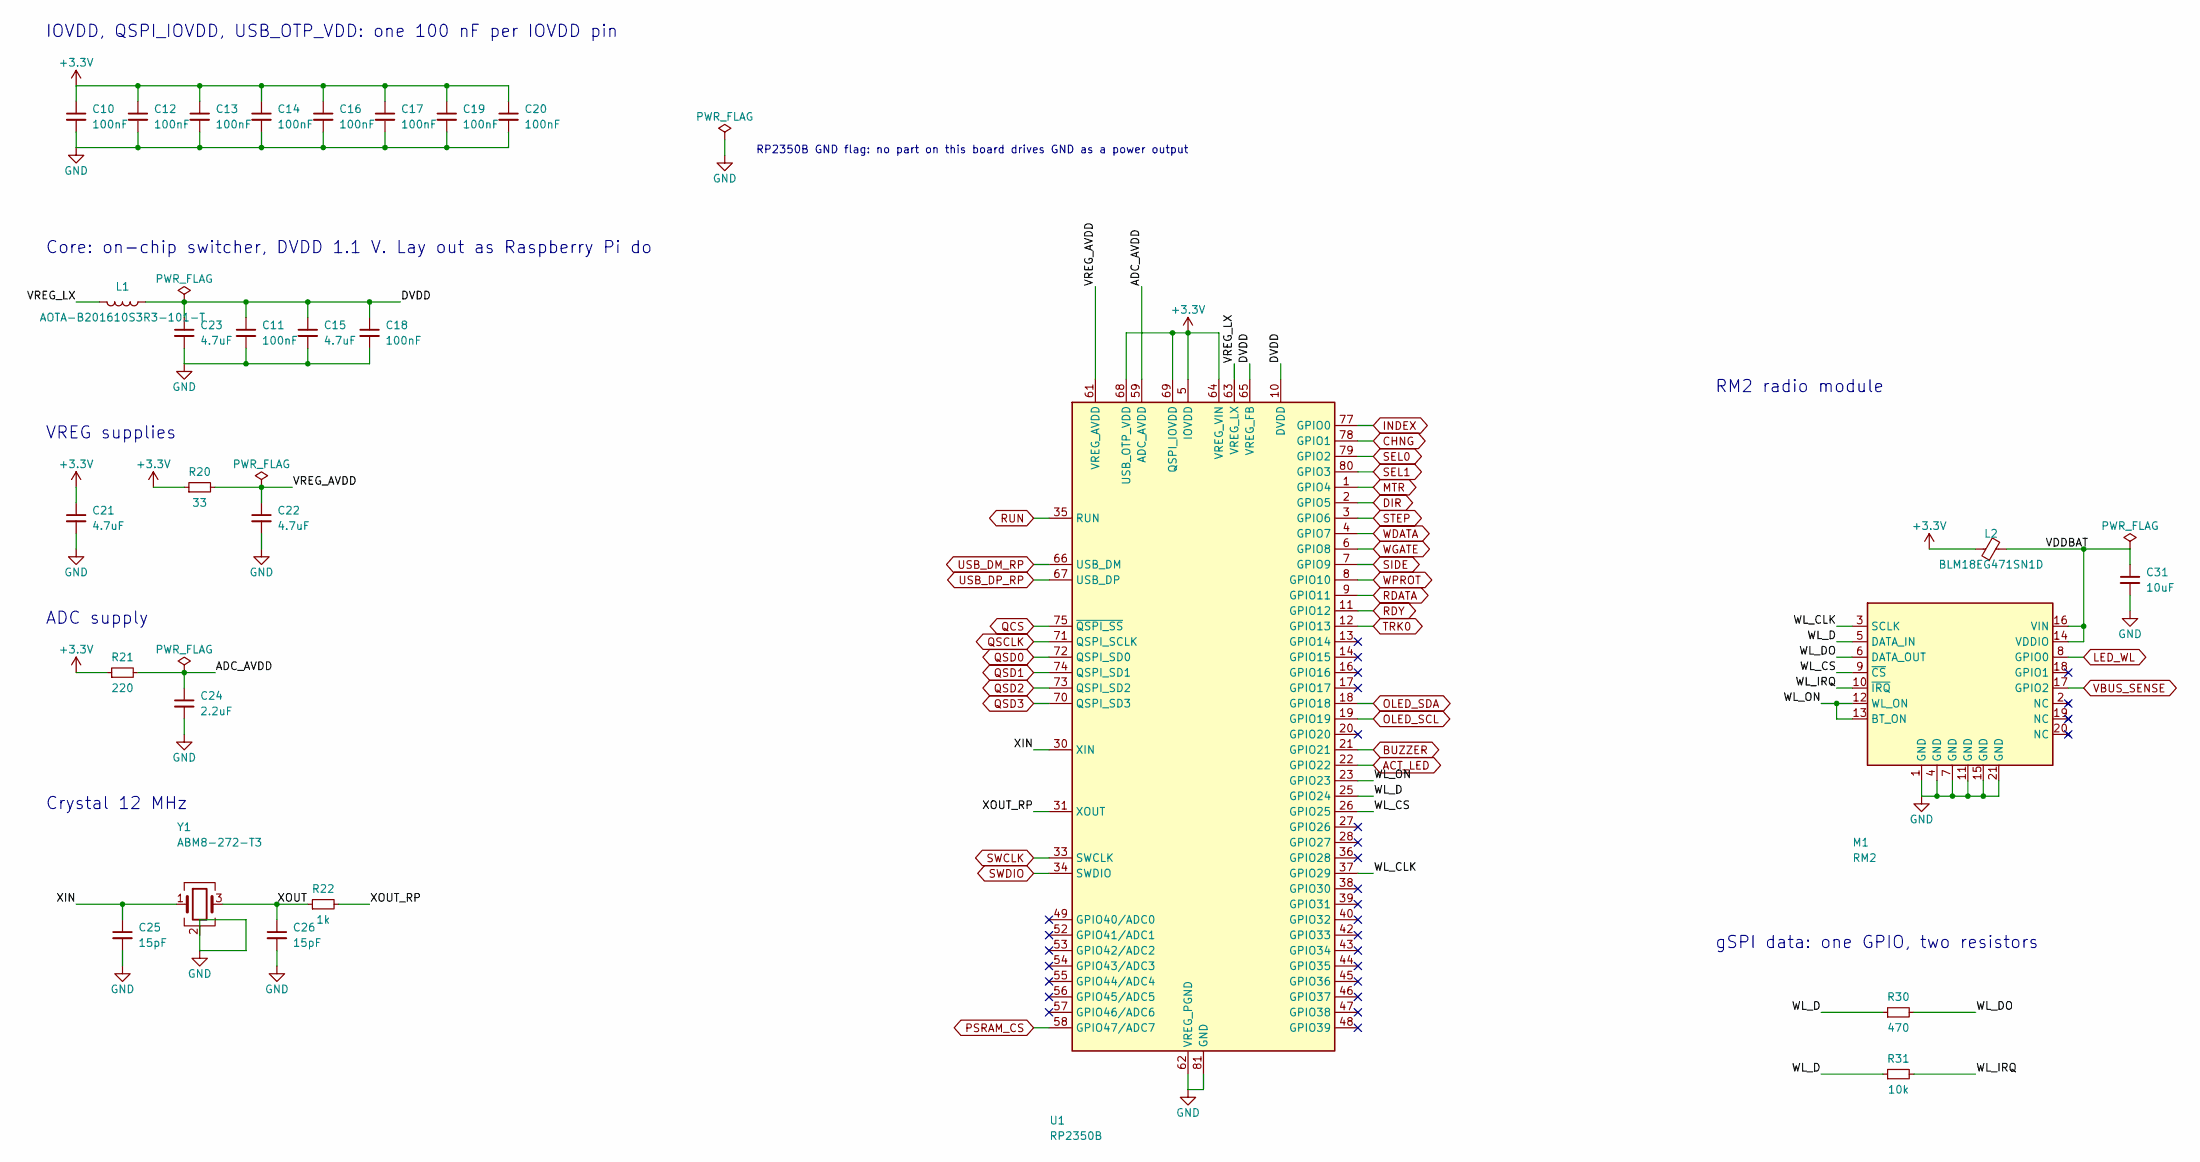
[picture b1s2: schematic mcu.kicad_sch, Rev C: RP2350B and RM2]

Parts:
C10, C11, C12, C13, C14, C16, C17, C18, C19, C20: 100nF; C_0402_1005Metric
C15, C22: 4.7uF; C_0402_1005Metric
C21, C23: 4.7uF; C_0402_1005Metric_RP_wide
C24: 2.2uF; C_0603_1608Metric
C25, C26: 15pF; C_0402_1005Metric
C31: 10uF; C_0603_1608Metric
L1: AOTA-B201610S3R3-101-T; L_Abracon_AOTA-B201610S3R3-101-T; MPN AOTA-B201610S3R3-101-T
L2: BLM18EG471SN1D; L_0603_1608Metric; MPN BLM18EG471SN1D
M1: RM2; Raspberry_Pi_RM2; MPN Raspberry Pi RM2
R20: 33; R_0402_1005Metric
R21: 220; R_0402_1005Metric
R22: 1k; R_0402_1005Metric
R30: 470; R_0402_1005Metric
R31: 10k; R_0402_1005Metric
U1: RP2350B; QFN-80-1EP_10x10mm_P0.4mm_EP3.4x3.4mm_ThermalVias; MPN RP2350B
Y1: ABM8-272-T3; Crystal_SMD_3225-4Pin_3.2x2.5mm

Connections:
+3.3V: C10.1, C12.1, C13.1, C14.1, C16.1, C17.1, C19.1, C20.1, C21.1, L2.1, R20.1, R21.1, U1.5 (IOVDD), U1.15 (IOVDD), U1.24 (IOVDD), U1.29 (IOVDD), U1.41 (IOVDD), U1.50 (IOVDD), U1.60 (IOVDD), U1.64 (VREG_VIN), U1.68 (USB_OTP_VDD), U1.69 (QSPI_IOVDD), U1.76 (IOVDD); also elsewhere on the board
/MCU/ADC_AVDD: C24.1, R21.2, U1.59 (ADC_AVDD)
/MCU/DVDD: C11.1, C15.1, C18.1, C23.1, L1.1, U1.10 (DVDD), U1.32 (DVDD), U1.51 (DVDD), U1.65 (VREG_FB)
/MCU/VDDBAT: C31.1, L2.2, M1.14 (VDDIO), M1.16 (VIN)
/MCU/VREG_AVDD: C22.1, R20.2, U1.61 (VREG_AVDD)
/MCU/VREG_LX: L1.2, U1.63 (VREG_LX)
/MCU/WL_CLK: M1.3 (SCLK), U1.37 (GPIO29)
/MCU/WL_CS: M1.9 (~CS), U1.26 (GPIO25)
/MCU/WL_D: M1.5 (DATA_IN), R30.1, R31.1, U1.25 (GPIO24)
/MCU/WL_DO: M1.6 (DATA_OUT), R30.2
/MCU/WL_IRQ: M1.10 (~IRQ), R31.2
/MCU/WL_ON: M1.12 (WL_ON), M1.13 (BT_ON), U1.23 (GPIO23)
/MCU/XIN: C25.1, U1.30 (XIN), Y1.1
/MCU/XOUT: C26.1, R22.1, Y1.3
/MCU/XOUT_RP: R22.2, U1.31 (XOUT)
ACT_LED: U1.22 (GPIO22); also elsewhere on the board
BUZZER: U1.21 (GPIO21); also elsewhere on the board
CHNG: U1.78 (GPIO1); also elsewhere on the board
DIR: U1.2 (GPIO5); also elsewhere on the board
GND: C10.2, C11.2, C12.2, C13.2, C14.2, C15.2, C16.2, C17.2, C18.2, C19.2, C20.2, C21.2, C22.2, C23.2, C24.2, C25.2, C26.2, C31.2, M1.1 (GND), M1.4 (GND), M1.7 (GND), M1.11 (GND), M1.15 (GND), M1.21 (GND), U1.62 (VREG_PGND), U1.81 (GND), Y1.2 (G), Y1.4 (G); also elsewhere on the board
INDEX: U1.77 (GPIO0); also elsewhere on the board
LED_WL: M1.8 (GPIO0); also elsewhere on the board
MTR: U1.1 (GPIO4); also elsewhere on the board
OLED_SCL: U1.19 (GPIO19); also elsewhere on the board
OLED_SDA: U1.18 (GPIO18); also elsewhere on the board
PSRAM_CS: U1.58 (GPIO47/ADC7); also elsewhere on the board
QCS: U1.75 (~QSPI_SS); also elsewhere on the board
QSCLK: U1.71 (QSPI_SCLK); also elsewhere on the board
QSD0: U1.72 (QSPI_SD0); also elsewhere on the board
QSD1: U1.74 (QSPI_SD1); also elsewhere on the board
QSD2: U1.73 (QSPI_SD2); also elsewhere on the board
QSD3: U1.70 (QSPI_SD3); also elsewhere on the board
RDATA: U1.9 (GPIO11); also elsewhere on the board
RDY: U1.11 (GPIO12); also elsewhere on the board
RUN: U1.35 (RUN); also elsewhere on the board
SEL0: U1.79 (GPIO2); also elsewhere on the board
SEL1: U1.80 (GPIO3); also elsewhere on the board
SIDE: U1.7 (GPIO9); also elsewhere on the board
STEP: U1.3 (GPIO6); also elsewhere on the board
SWCLK: U1.33 (SWCLK); also elsewhere on the board
SWDIO: U1.34 (SWDIO); also elsewhere on the board
TRK0: U1.12 (GPIO13); also elsewhere on the board
USB_DM_RP: U1.66 (USB_DM); also elsewhere on the board
USB_DP_RP: U1.67 (USB_DP); also elsewhere on the board
VBUS_SENSE: M1.17 (GPIO2); also elsewhere on the board
WDATA: U1.4 (GPIO7); also elsewhere on the board
WGATE: U1.6 (GPIO8); also elsewhere on the board
WPROT: U1.8 (GPIO10); also elsewhere on the board

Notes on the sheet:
Crystal 12 MHz
RP2350B GND flag: no part on this board drives GND as a power output
ADC supply
gSPI data: one GPIO, two resistors
VREG supplies
RM2 radio module
IOVDD, QSPI_IOVDD, USB_OTP_VDD: one 100 nF per IOVDD pin
Core: on-chip switcher, DVDD 1.1 V. Lay out as Raspberry Pi do

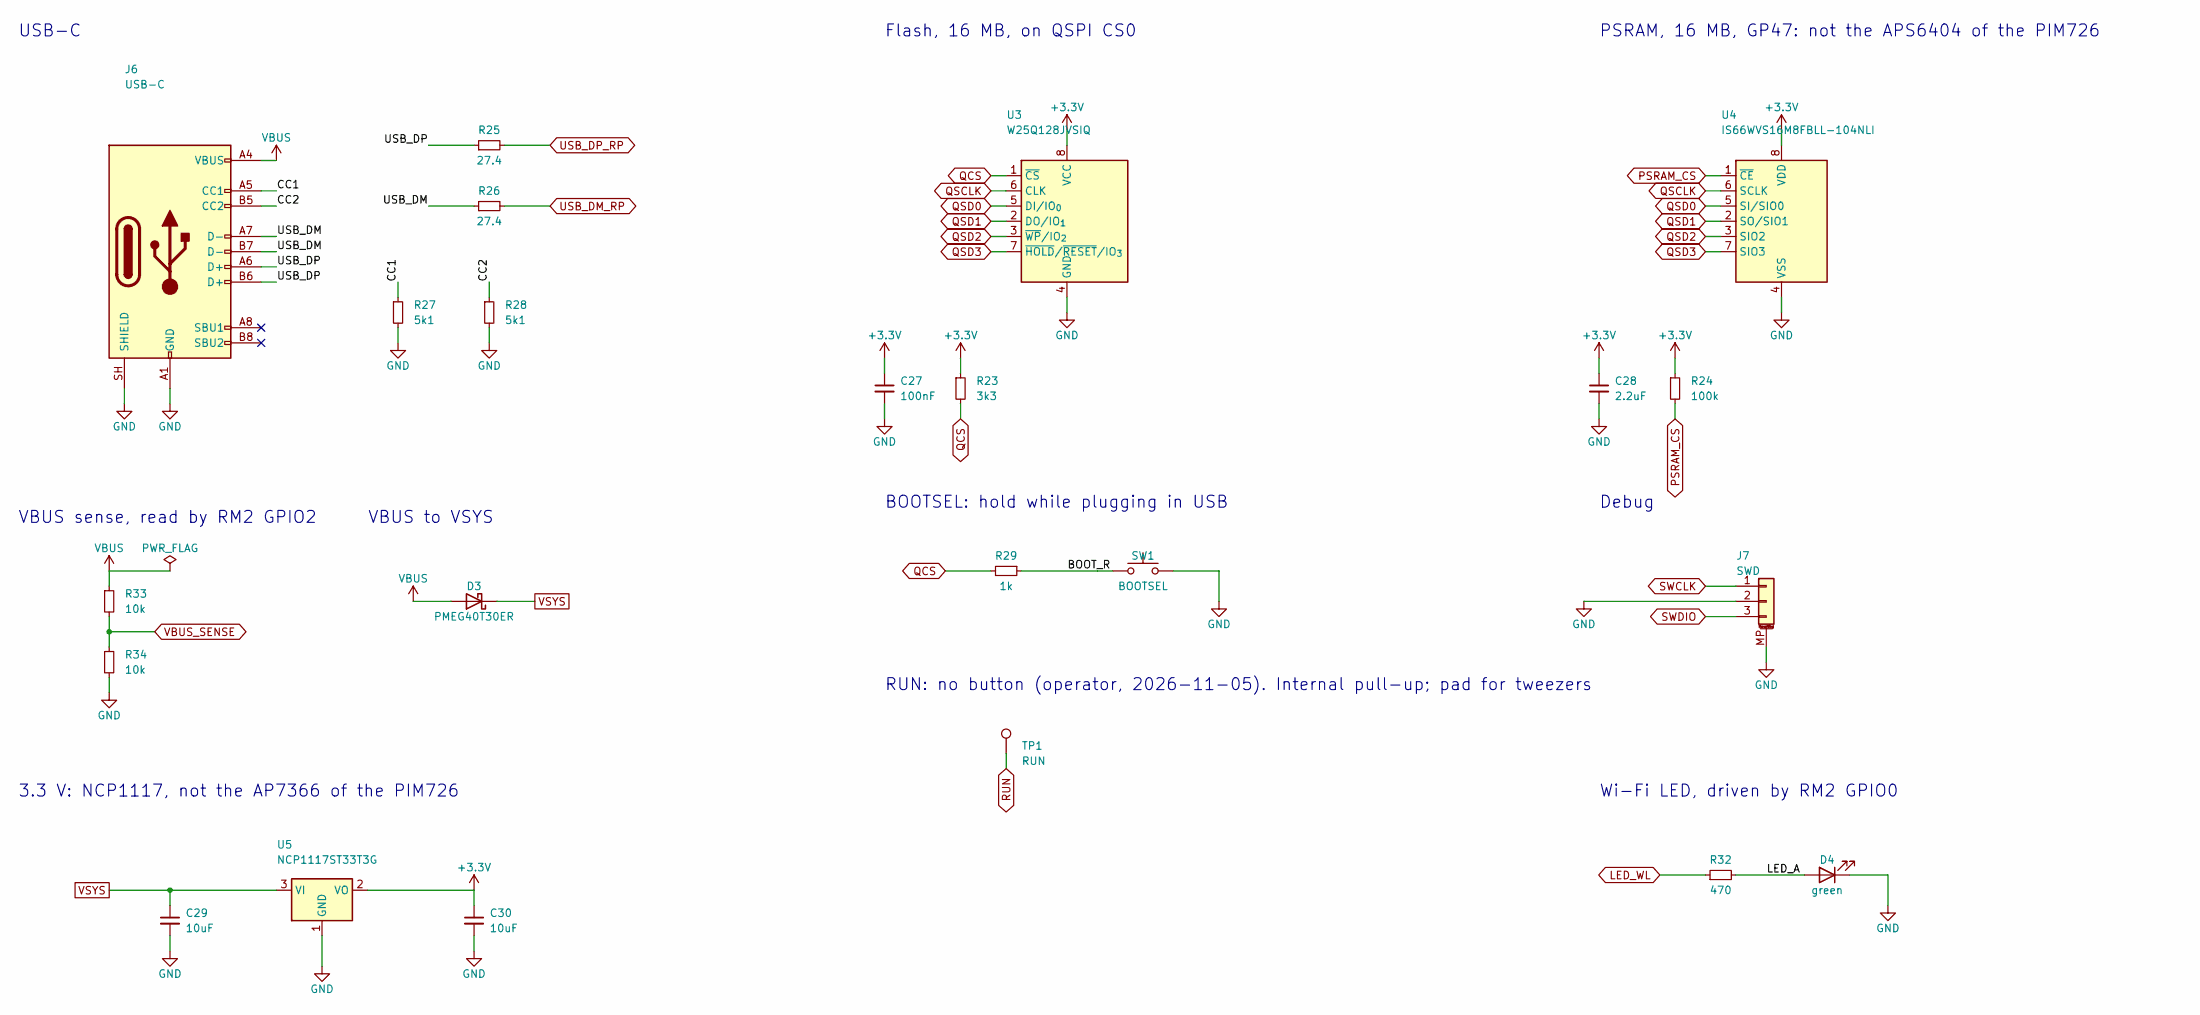
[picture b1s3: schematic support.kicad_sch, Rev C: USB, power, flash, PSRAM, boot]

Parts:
C27: 100nF; C_0402_1005Metric
C28: 2.2uF; C_0603_1608Metric
C29, C30: 10uF; C_0603_1608Metric
D3: PMEG40T30ER; D_SOD-123F; MPN PMEG40T30ER
D4: green; LED_0603_1608Metric
J6: USB-C; USB_C_Receptacle_HRO_TYPE-C-31-M-12; MPN HRO TYPE-C-31-M-12
J7: SWD; JST_SH_BM03B-SRSS-TB_1x03-1MP_P1.00mm_Vertical; MPN JST BM03B-SRSS-TB
R23: 3k3; R_0402_1005Metric
R24: 100k; R_0402_1005Metric
R25, R26: 27.4; R_0402_1005Metric
R27, R28: 5k1; R_0402_1005Metric
R29: 1k; R_0402_1005Metric
R32: 470; R_0402_1005Metric
R33, R34: 10k; R_0402_1005Metric
SW1: BOOTSEL; SW_Push_1P1T_XKB_TS-1187A; MPN XKB TS-1187A
TP1: RUN; TestPoint_Pad_D1.0mm
U3: W25Q128JVSIQ; SOIC-8_5.3x5.3mm_P1.27mm; MPN W25Q128JVSIQ
U4: IS66WVS16M8FBLL-104NLI; SOIC-8_3.9x4.9mm_P1.27mm; MPN IS66WVS16M8FBLL-104NLI
U5: NCP1117ST33T3G; SOT-223-3_TabPin2; MPN NCP1117ST33T3G

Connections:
+3.3V: C27.1, C28.1, C30.1, R23.1, R24.1, U3.8 (VCC), U4.8 (VDD), U5.2 (VO); also elsewhere on the board
/Support/BOOT_R: R29.1, SW1.1
/Support/CC1: J6.A5 (CC1), R27.1
/Support/CC2: J6.B5 (CC2), R28.1
/Support/LED_A: D4.2 (A), R32.2
/Support/USB_DM: J6.A7 (D-), J6.B7 (D-), R26.1
/Support/USB_DP: J6.A6 (D+), J6.B6 (D+), R25.1
GND: C27.2, C28.2, C29.2, C30.2, D4.1 (K), J6.A1 (GND), J6.A12 (GND), J6.B1 (GND), J6.B12 (GND), J6.SH (SHIELD), J7.2, J7.MP (MountPin), R27.2, R28.2, R34.2, SW1.2, U3.4 (GND), U4.4 (VSS), U5.1 (GND); also elsewhere on the board
LED_WL: R32.1; also elsewhere on the board
PSRAM_CS: R24.2, U4.1 (~CE); also elsewhere on the board
QCS: R23.2, R29.2, U3.1 (~CS); also elsewhere on the board
QSCLK: U3.6 (CLK), U4.6 (SCLK); also elsewhere on the board
QSD0: U3.5 (DI/IO_{0}), U4.5 (SI/SIO0); also elsewhere on the board
QSD1: U3.2 (DO/IO_{1}), U4.2 (SO/SIO1); also elsewhere on the board
QSD2: U3.3 (~WP/IO_{2}), U4.3 (SIO2); also elsewhere on the board
QSD3: U3.7 (~HOLD/~RESET/IO_{3}), U4.7 (SIO3); also elsewhere on the board
RUN: TP1.1; also elsewhere on the board
SWCLK: J7.1; also elsewhere on the board
SWDIO: J7.3; also elsewhere on the board
USB_DM_RP: R26.2; also elsewhere on the board
USB_DP_RP: R25.2; also elsewhere on the board
VBUS: D3.2 (A), J6.A4 (VBUS), J6.A9 (VBUS), J6.B4 (VBUS), J6.B9 (VBUS), R33.1
VBUS_SENSE: R33.2, R34.1; also elsewhere on the board
VSYS: C29.1, D3.1 (K), U5.3 (VI); also elsewhere on the board

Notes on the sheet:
VBUS to VSYS
PSRAM, 16 MB, GP47: not the APS6404 of the PIM726
Flash, 16 MB, on QSPI CS0
BOOTSEL: hold while plugging in USB
Debug
USB-C
VBUS sense, read by RM2 GPIO2
3.3 V: NCP1117, not the AP7366 of the PIM726
Wi-Fi LED, driven by RM2 GPIO0
RUN: no button (operator, 2026-11-05). Internal pull-up; pad for tweezers

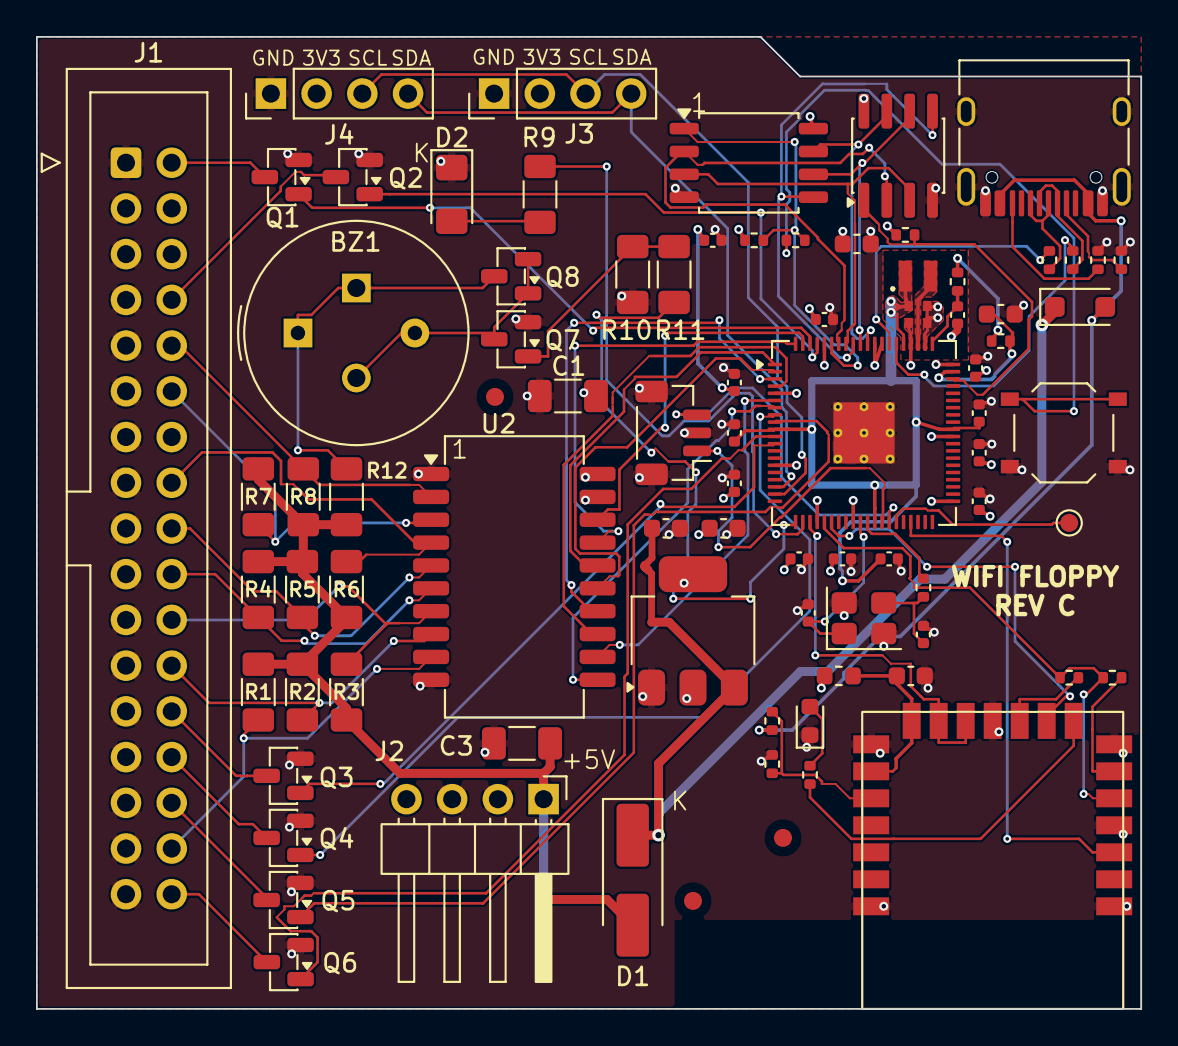
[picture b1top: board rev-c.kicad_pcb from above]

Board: 4 copper layers, 61.4 x 54.0 mm, 84 parts (0 on the bottom side), 75 nets.

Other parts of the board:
FID1, FID2, FID3: Fiducial_1mm_Mask2mm
